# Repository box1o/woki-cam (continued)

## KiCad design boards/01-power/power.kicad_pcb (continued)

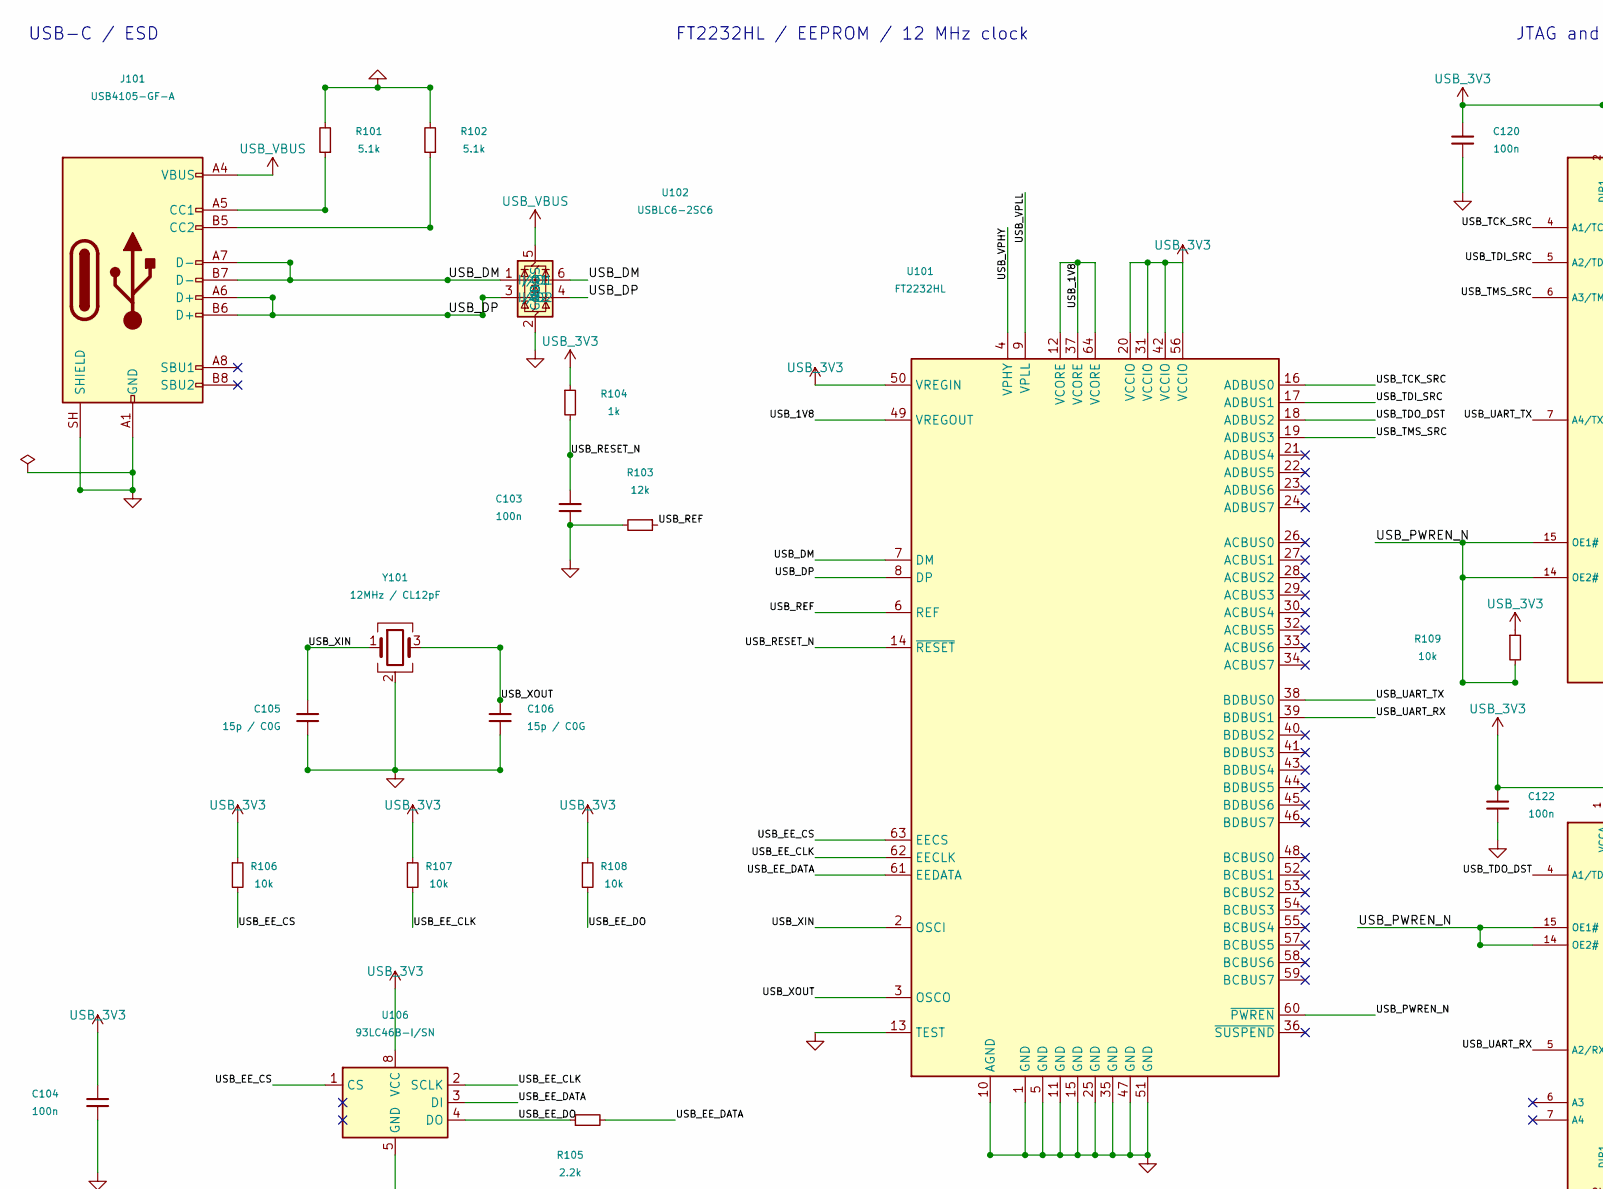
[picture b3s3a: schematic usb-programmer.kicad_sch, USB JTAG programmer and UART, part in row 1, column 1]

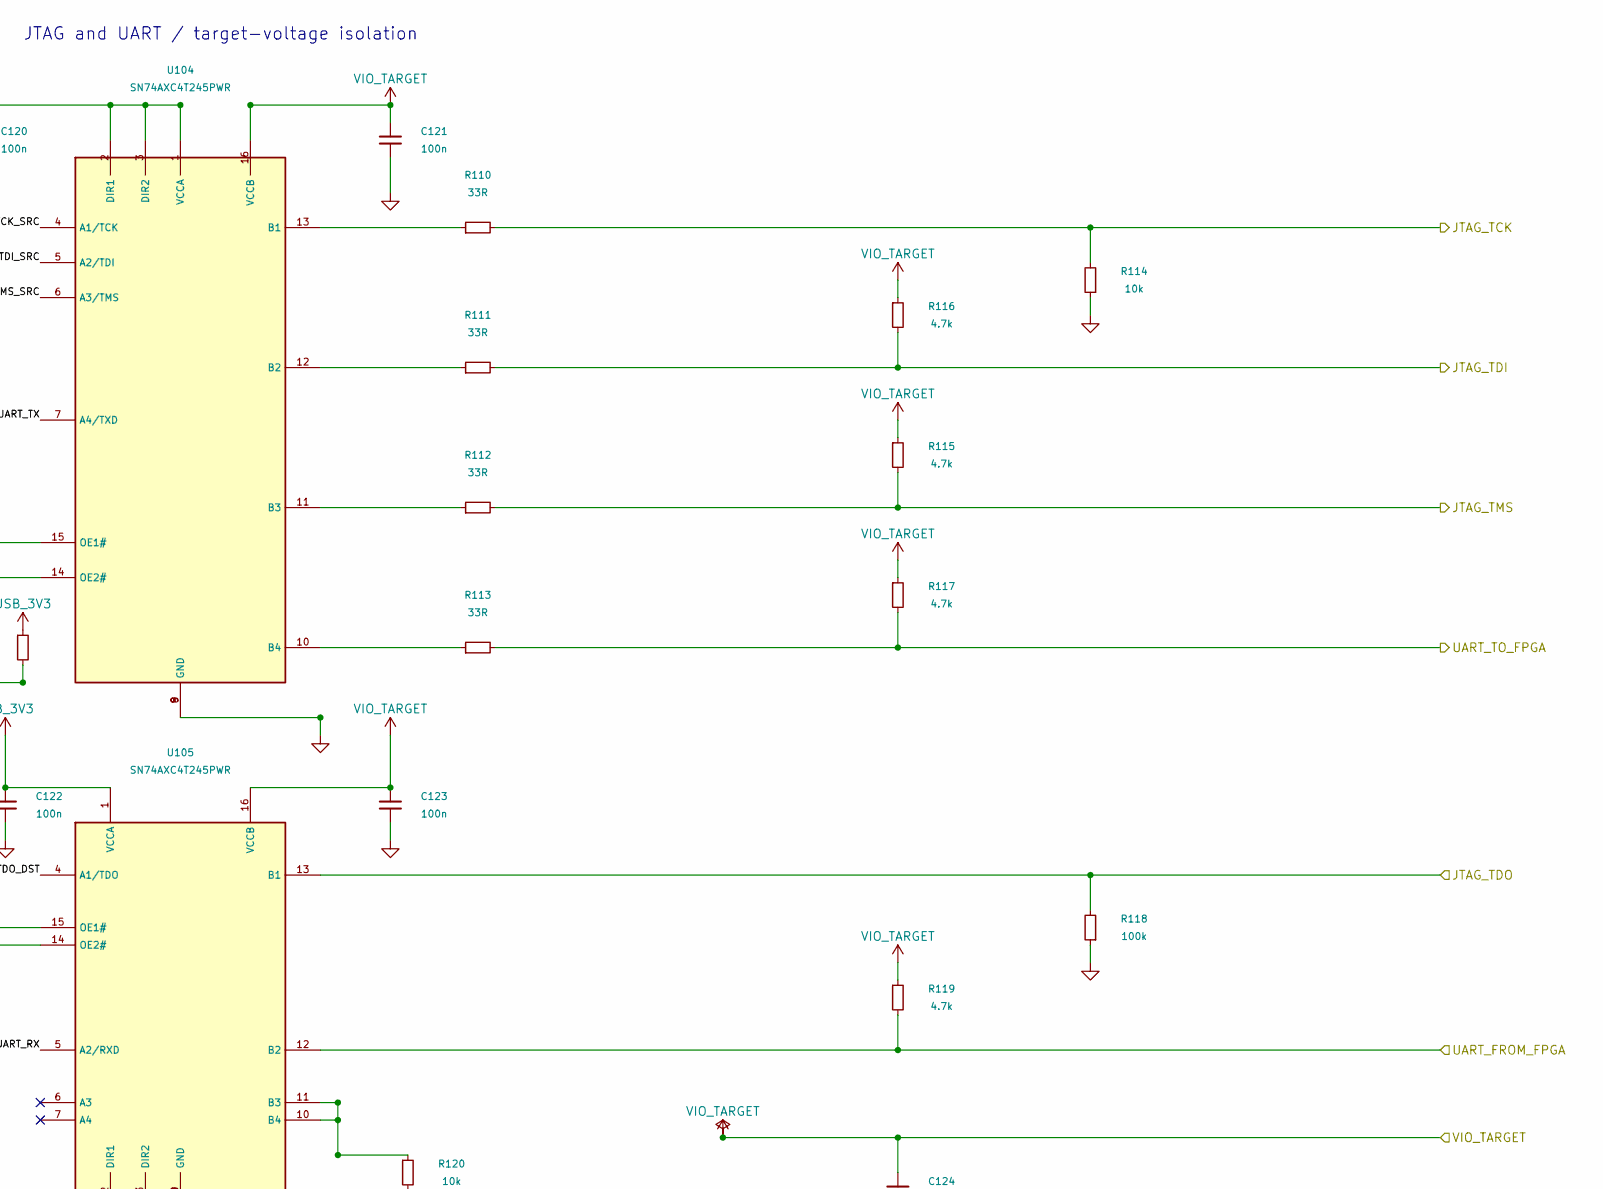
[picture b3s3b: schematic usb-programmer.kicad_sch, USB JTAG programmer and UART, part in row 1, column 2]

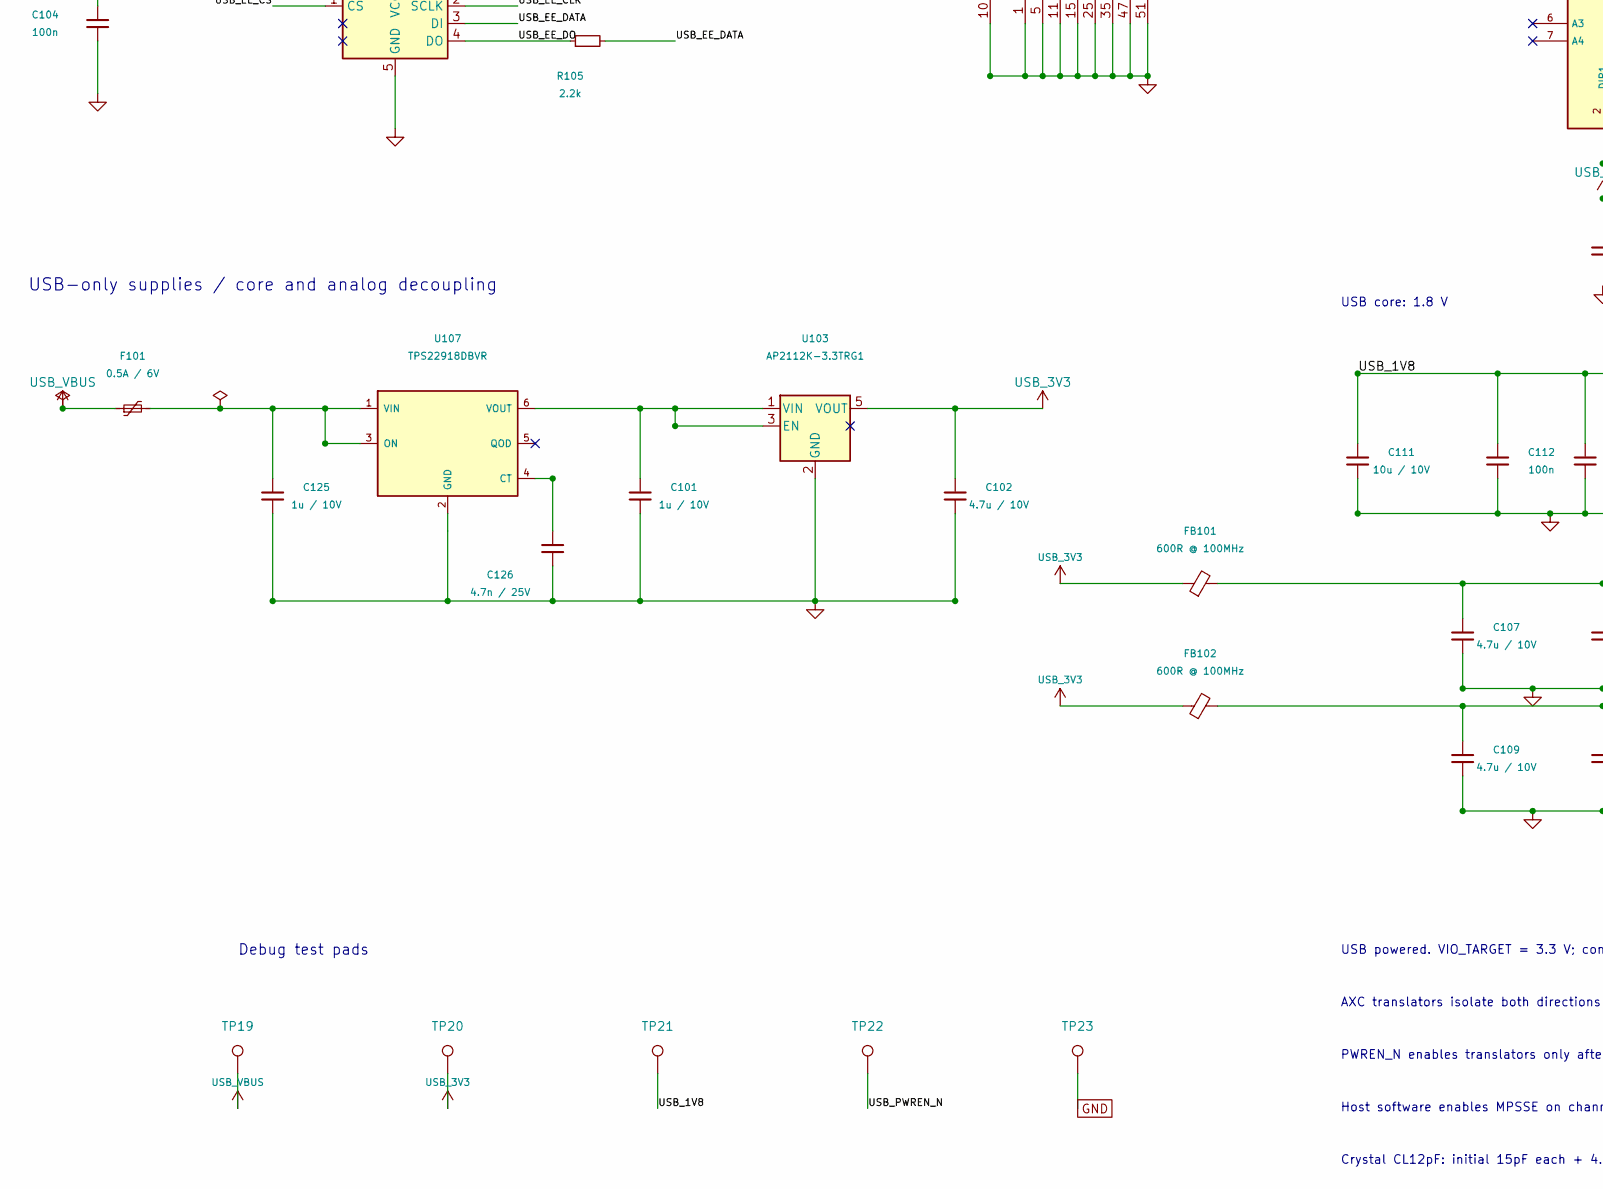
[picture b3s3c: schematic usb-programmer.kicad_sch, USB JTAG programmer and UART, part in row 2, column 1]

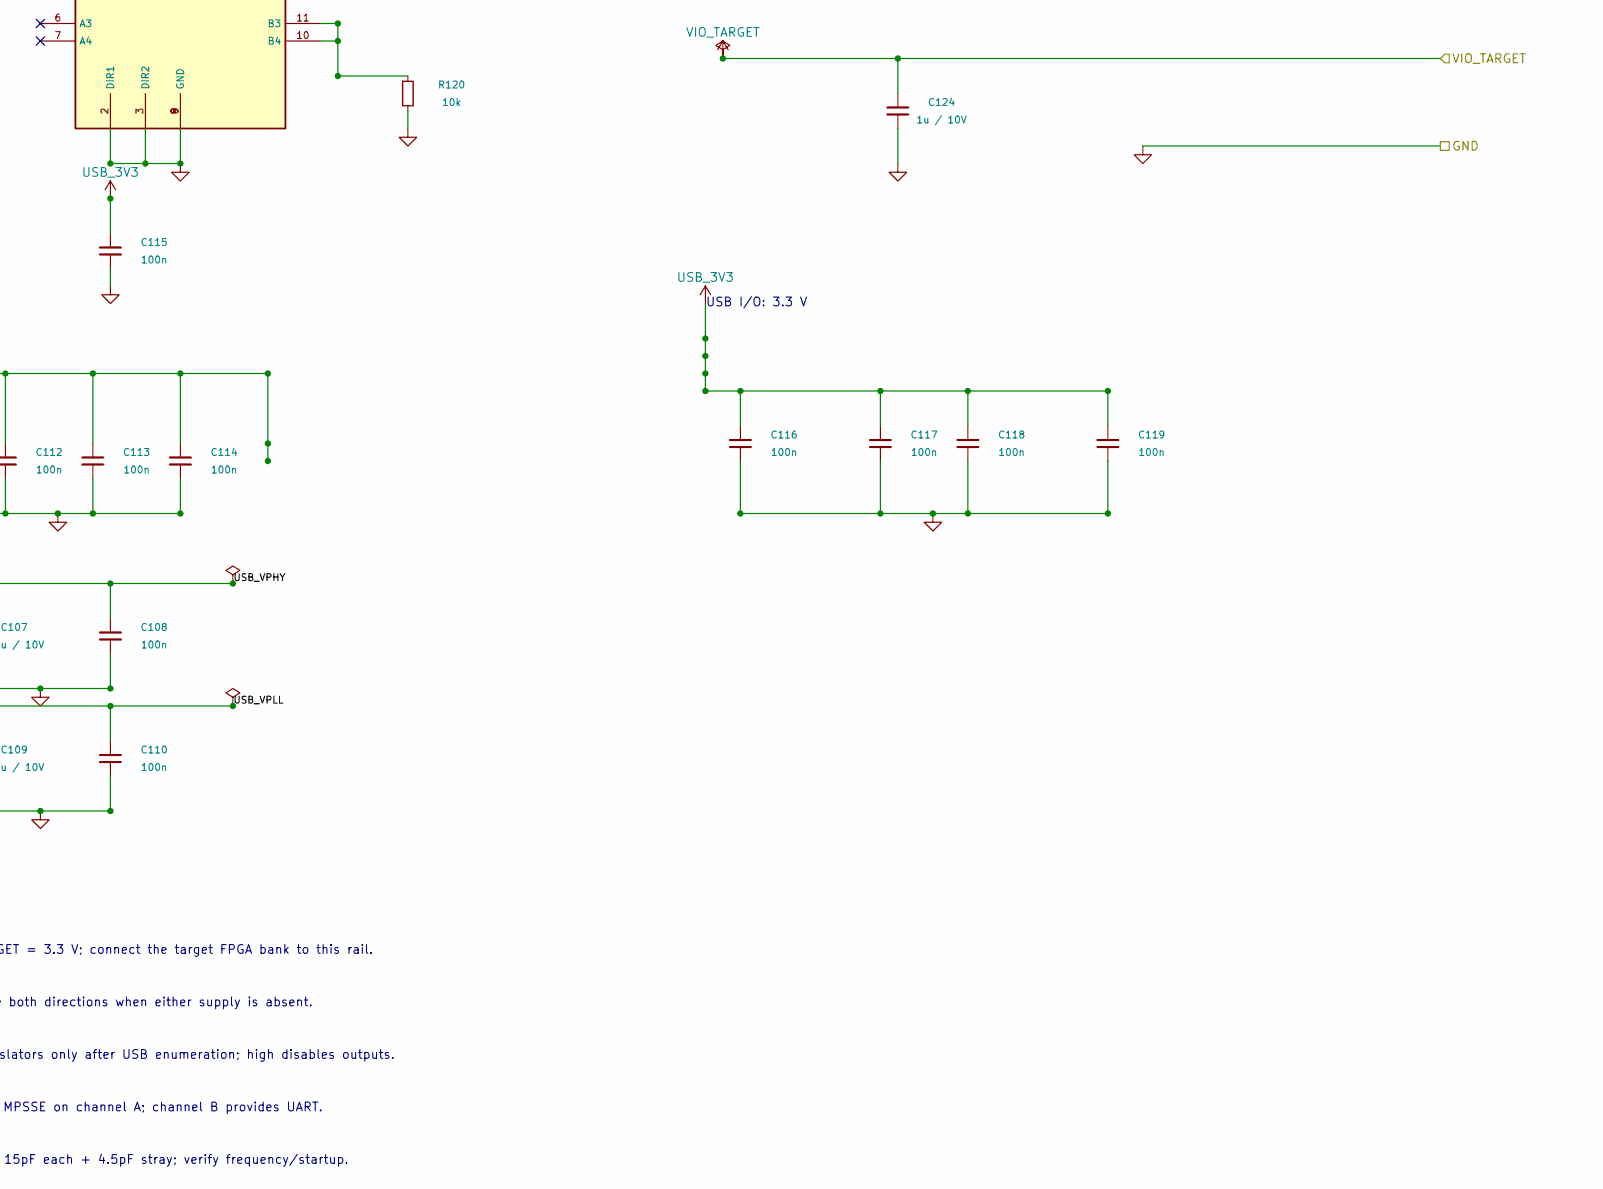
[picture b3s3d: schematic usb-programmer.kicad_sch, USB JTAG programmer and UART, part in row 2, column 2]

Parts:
C101, C124, C125: 1u / 10V; C_0603_1608Metric
C102, C107, C109: 4.7u / 10V; C_0603_1608Metric
C103, C104, C108, C110, C112, C113, C114, C115, C116, C117, C118, C119, C120, C121, C122, C123: 100n; C_0603_1608Metric
C105, C106: 15p / C0G; C_0603_1608Metric
C111: 10u / 10V; C_0805_2012Metric
C126: 4.7n / 25V; C_0603_1608Metric
F101: 0.5A / 6V; Fuse_1206_3216Metric
FB101, FB102: 600R @ 100MHz; L_0603_1608Metric
J101: USB4105-GF-A; USB_C_Receptacle_GCT_USB4105-xx-A_16P_TopMnt_Horizontal
R101, R102: 5.1k; R_0603_1608Metric
R103: 12k; R_0603_1608Metric
R104: 1k; R_0603_1608Metric
R105: 2.2k; R_0603_1608Metric
R106, R107, R108, R109, R114, R120: 10k; R_0603_1608Metric
R110, R111, R112, R113: 33R; R_0603_1608Metric
R115, R116, R117, R119: 4.7k; R_0603_1608Metric
R118: 100k; R_0603_1608Metric
TP19: USB_VBUS; testpoint-pad-1.5mm
TP20: USB_3V3; testpoint-pad-1.5mm
TP21: USB_1V8; testpoint-pad-1.5mm
TP22: USB_PWREN_N; testpoint-pad-1.5mm
TP23: GND; testpoint-pad-1.5mm
U101: FT2232HL; LQFP-64_10x10mm_P0.5mm
U102: USBLC6-2SC6; SOT-23-6
U103: AP2112K-3.3TRG1; SOT-23-5
U104, U105: SN74AXC4T245PWR; TSSOP-16_4.4x5mm_P0.65mm
U106: 93LC46B-I/SN; SOIC-8_3.9x4.9mm_P1.27mm
U107: TPS22918DBVR; SOT-23-6
Y101: 12MHz / CL12pF; Crystal_SMD_3225-4Pin_3.2x2.5mm; MPN ABM8-12.000MHZ-12-B1U-T

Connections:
/JTAG_TCK: R110.2, R114.2; also elsewhere on the board
/JTAG_TDI: R111.2, R116.2; also elsewhere on the board
/JTAG_TDO: R118.2, U105.13 (B1); also elsewhere on the board
/JTAG_TMS: R112.2, R115.2; also elsewhere on the board
/UART_FROM_FPGA: R119.2, U105.12 (B2); also elsewhere on the board
/UART_TO_FPGA: R113.2, R117.2; also elsewhere on the board
/USB JTAG / UART/USB_1V8: C111.1, C112.1, C113.1, C114.1, TP21.1 (1_1), U101.12 (VCORE), U101.37 (VCORE), U101.49 (VREGOUT), U101.64 (VCORE)
/USB JTAG / UART/USB_DM: J101.A7 (D-), J101.B7 (D-), U101.7 (DM), U102.1 (I/O1), U102.6 (I/O1)
/USB JTAG / UART/USB_DP: J101.A6 (D+), J101.B6 (D+), U101.8 (DP), U102.3 (I/O2), U102.4 (I/O2)
/USB JTAG / UART/USB_EE_CLK: R107.2, U101.62 (EECLK), U106.2 (SCLK)
/USB JTAG / UART/USB_EE_CS: R106.2, U101.63 (EECS), U106.1 (CS)
/USB JTAG / UART/USB_EE_DATA: R105.2, U101.61 (EEDATA), U106.3 (DI)
/USB JTAG / UART/USB_EE_DO: R105.1, R108.2, U106.4 (DO)
/USB JTAG / UART/USB_PWREN_N: R109.2, TP22.1 (1_1), U101.60 (~PWREN), U104.14 (OE2#), U104.15 (OE1#), U105.14 (OE2#), U105.15 (OE1#)
/USB JTAG / UART/USB_REF: R103.1, U101.6 (REF)
/USB JTAG / UART/USB_RESET_N: C103.1, R104.2, U101.14 (~RESET)
/USB JTAG / UART/USB_TCK_SRC: U101.16 (ADBUS0), U104.4 (A1/TCK)
/USB JTAG / UART/USB_TDI_SRC: U101.17 (ADBUS1), U104.5 (A2/TDI)
/USB JTAG / UART/USB_TDO_DST: U101.18 (ADBUS2), U105.4 (A1/TDO)
/USB JTAG / UART/USB_TMS_SRC: U101.19 (ADBUS3), U104.6 (A3/TMS)
/USB JTAG / UART/USB_UART_RX: U101.39 (BDBUS1), U105.5 (A2/RXD)
/USB JTAG / UART/USB_UART_TX: U101.38 (BDBUS0), U104.7 (A4/TXD)
/USB JTAG / UART/USB_VPHY: C107.1, C108.1, FB101.2, U101.4 (VPHY)
/USB JTAG / UART/USB_VPLL: C109.1, C110.1, FB102.2, U101.9 (VPLL)
/USB JTAG / UART/USB_XIN: C105.1, U101.2 (OSCI), Y101.1
/USB JTAG / UART/USB_XOUT: C106.1, U101.3 (OSCO), Y101.3
unnamed: J101.A5 (CC1), R101.1
unnamed: J101.B5 (CC2), R102.1
unnamed: C101.1, U103.1 (VIN), U103.3 (EN), U107.6 (VOUT)
unnamed: R110.1, U104.13 (B1)
unnamed: R111.1, U104.12 (B2)
unnamed: R112.1, U104.11 (B3)
unnamed: R113.1, U104.10 (B4)
unnamed: C126.1, U107.4 (CT)
unnamed: C125.1, F101.2, U107.1 (VIN), U107.3 (ON)
USB_3V3: C102.1, C104.1, C115.1, C116.1, C117.1, C118.1, C119.1, C120.1, C122.1, FB101.1, FB102.1, R104.1, R106.1, R107.1, R108.1, R109.1, TP20.1 (1_1), U101.20 (VCCIO), U101.31 (VCCIO), U101.42 (VCCIO), U101.50 (VREGIN), U101.56 (VCCIO), U103.5 (VOUT), U104.1 (VCCA), U104.2 (DIR1), U104.3 (DIR2), U105.1 (VCCA), U106.8 (VCC)
USB_VBUS: F101.1, J101.A4 (VBUS), J101.A9 (VBUS), J101.B4 (VBUS), J101.B9 (VBUS), TP19.1 (1_1), U102.5 (VBUS)
VIO_TARGET: C121.1, C123.1, C124.1, R115.1, R116.1, R117.1, R119.1, U104.16 (VCCB), U105.16 (VCCB); also elsewhere on the board

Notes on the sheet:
USB powered. VIO_TARGET = 3.3 V; connect the target FPGA bank to this rail.
USB core: 1.8 V
JTAG and UART / target-voltage isolation
USB-only supplies / core and analog decoupling
Debug test pads
Crystal CL12pF: initial 15pF each + 4.5pF stray; verify frequency/startup.
USB-C / ESD
Host software enables MPSSE on channel A; channel B provides UART.
USB I/O: 3.3 V
FT2232HL / EEPROM / 12 MHz clock
AXC translators isolate both directions when either supply is absent.
PWREN_N enables translators only after USB enumeration; high disables outputs.

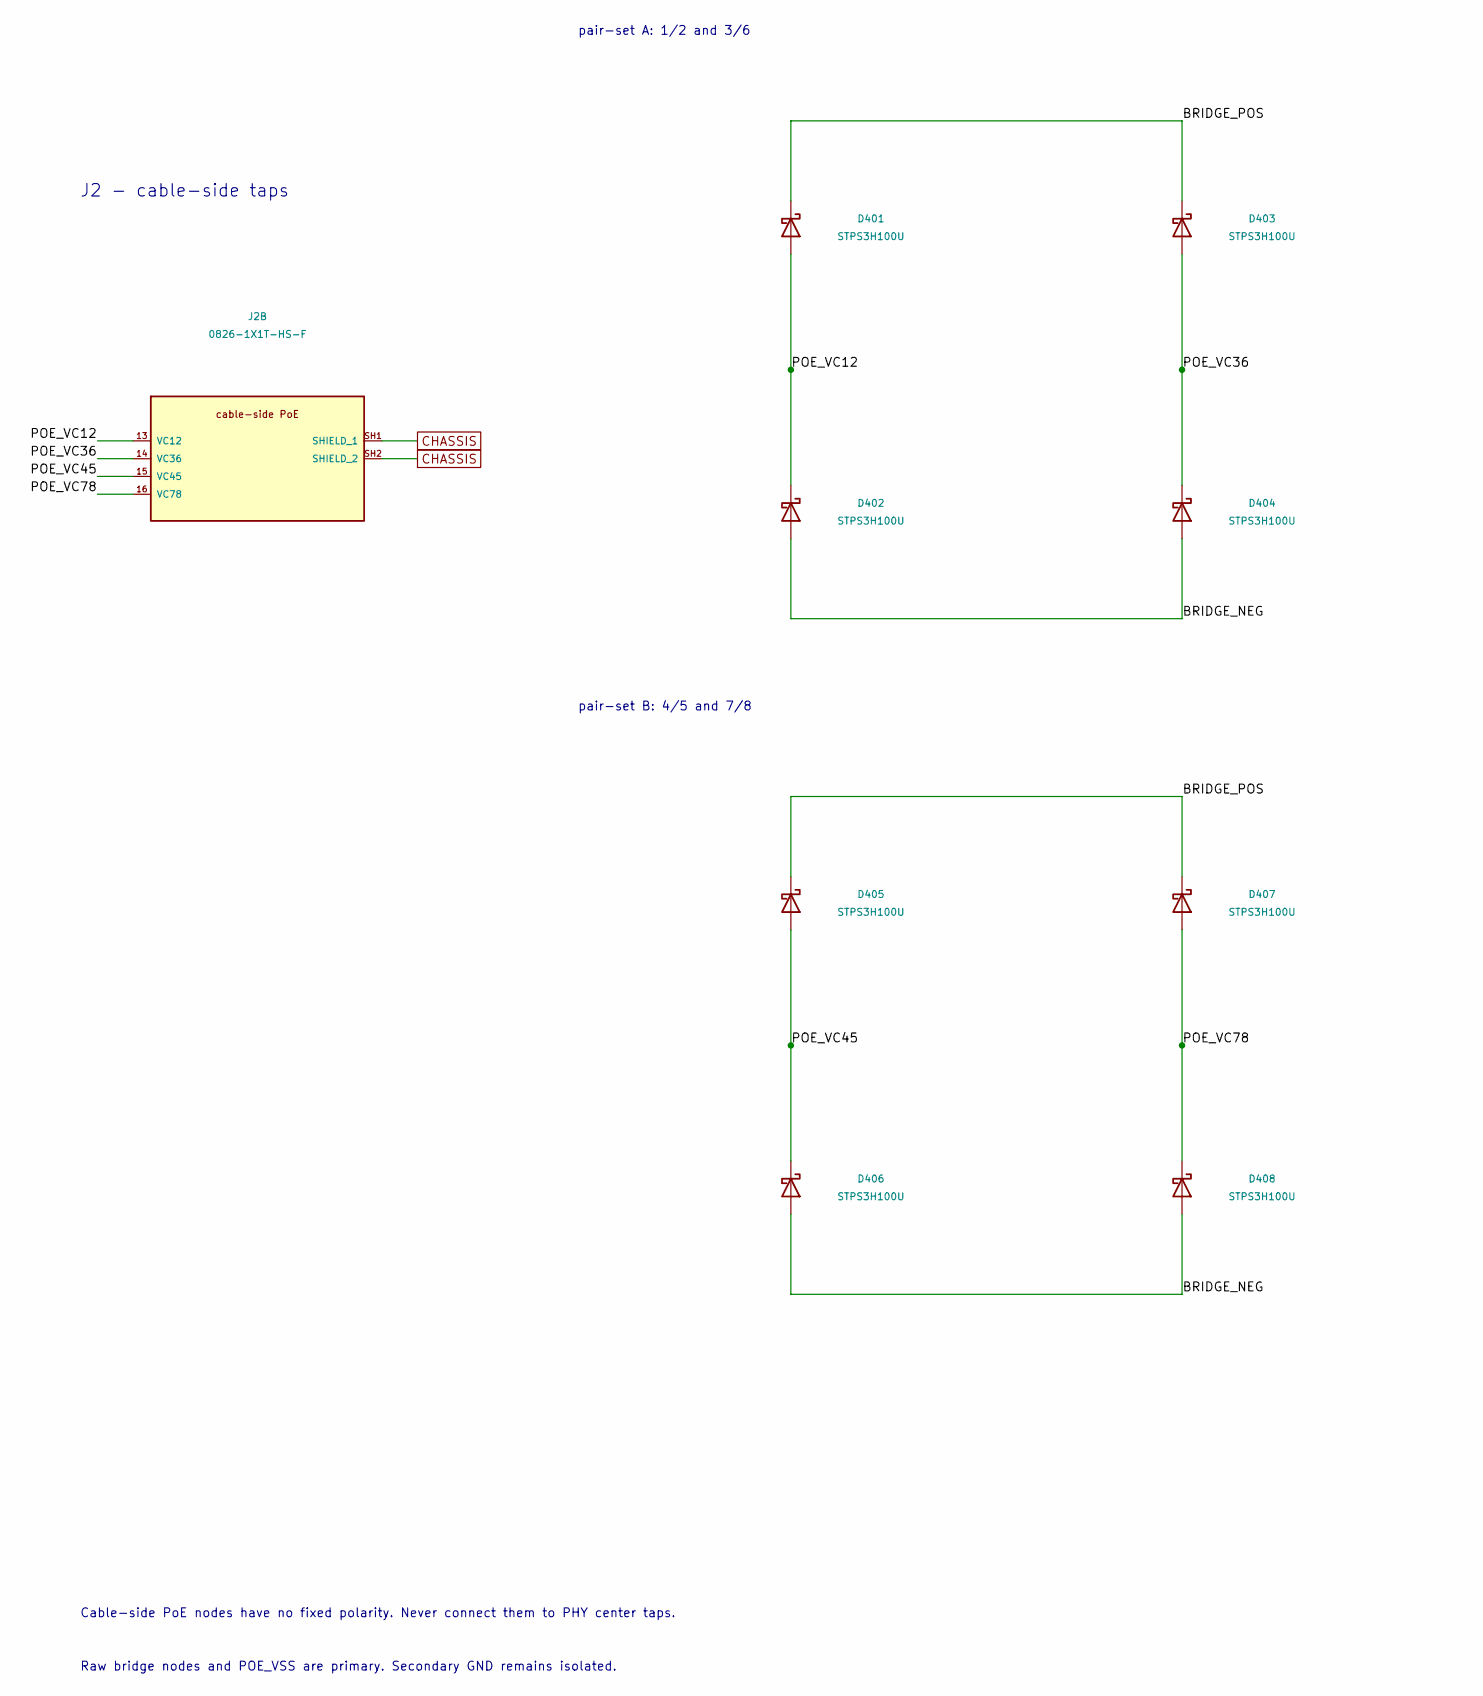
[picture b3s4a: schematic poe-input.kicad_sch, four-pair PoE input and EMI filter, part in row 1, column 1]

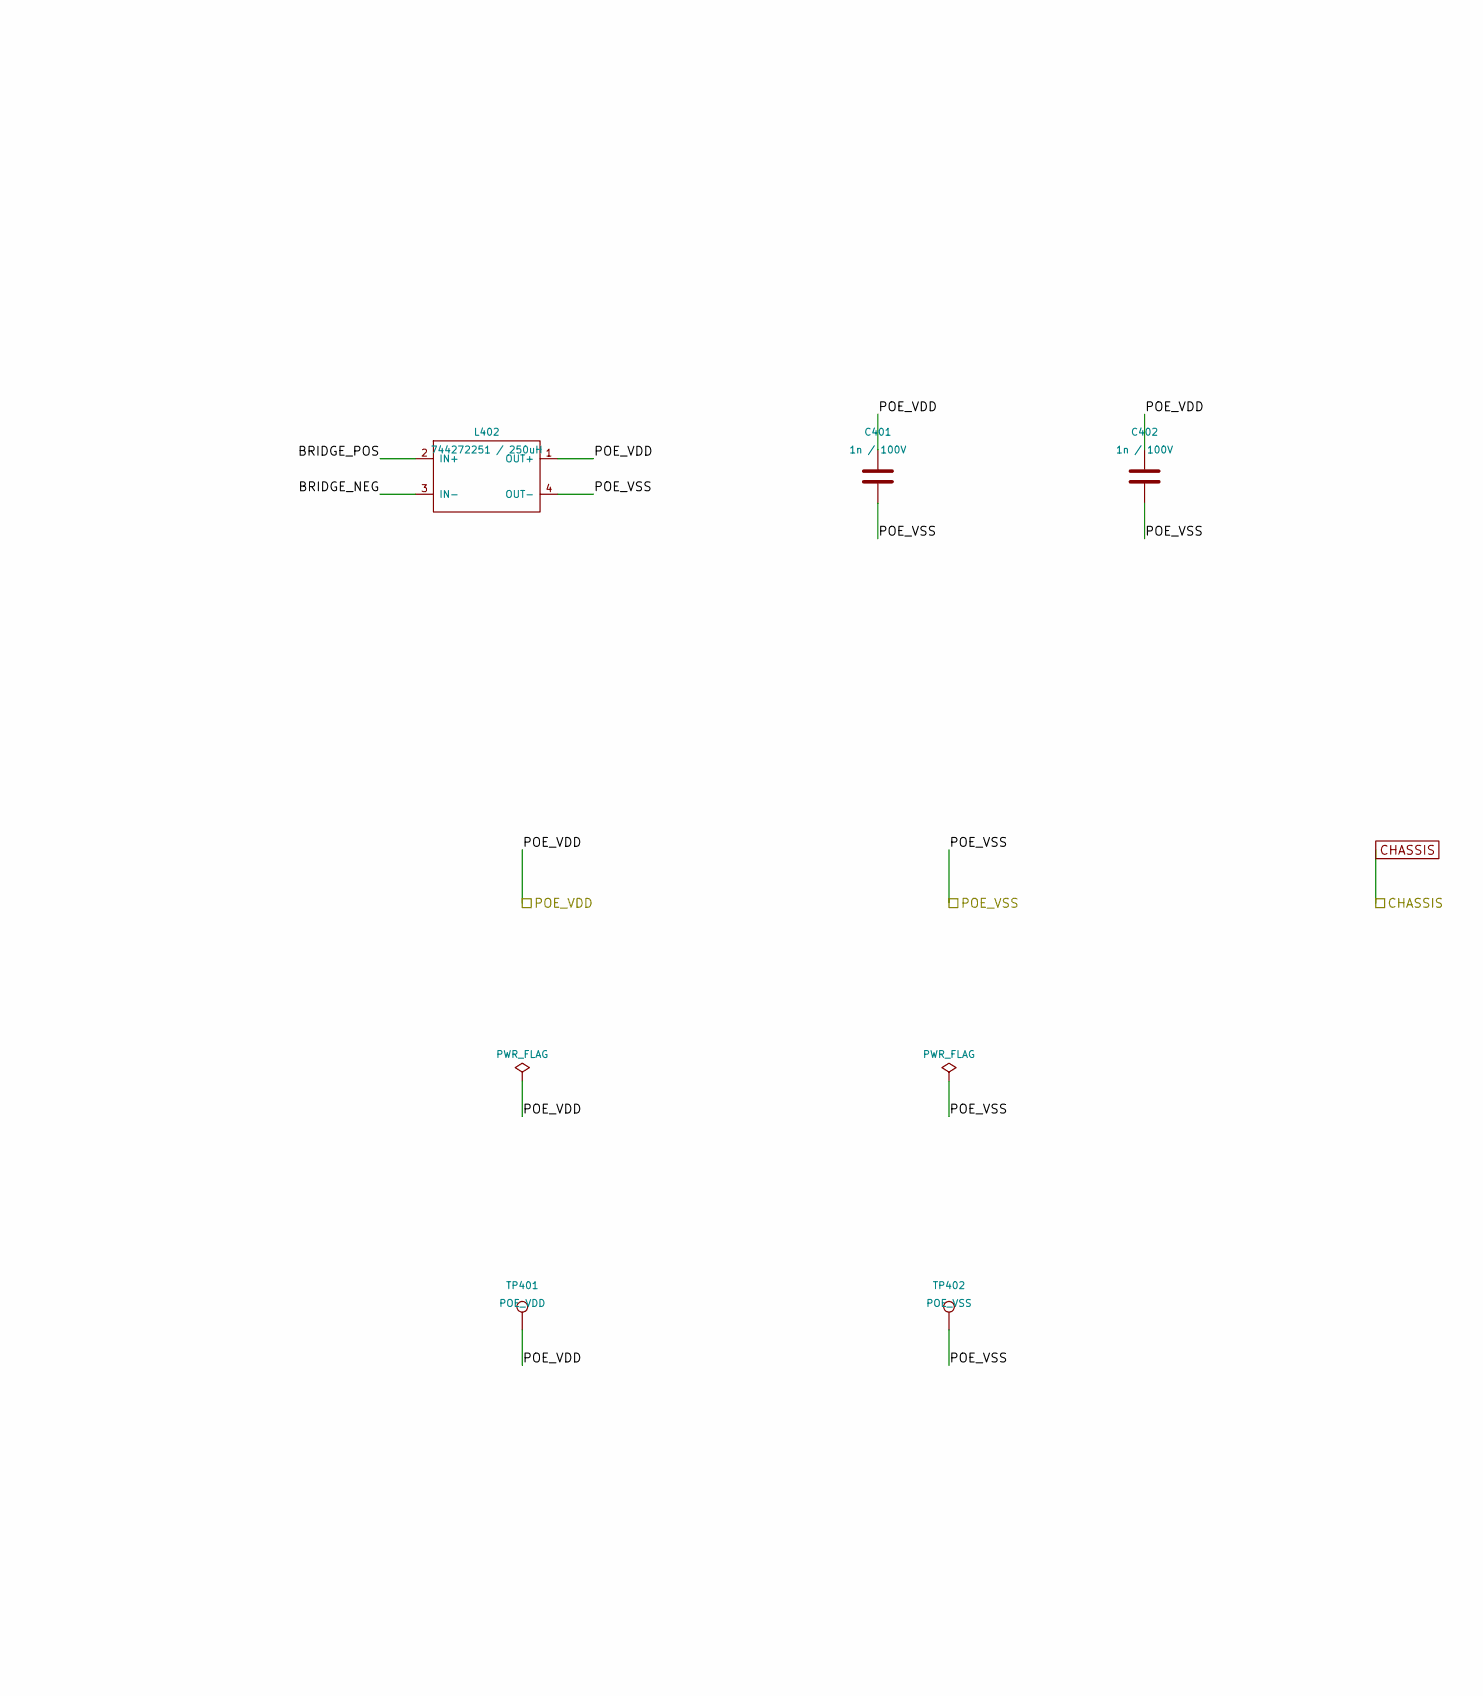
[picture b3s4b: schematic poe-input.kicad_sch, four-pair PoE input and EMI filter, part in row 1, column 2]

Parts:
C401, C402: 1n / 100V; C_0603_1608Metric
D401, D402, D403, D404, D405, D406, D407, D408: STPS3H100U; D_SMB
J2: 0826-1X1T-HS-F; 0826-1x1t-hs-f
L402: 744272251 / 250uH; 744272251
TP401: POE_VDD; TestPoint_Pad_D1.5mm
TP402: POE_VSS; TestPoint_Pad_D1.5mm

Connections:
/MagJack PoE input/BRIDGE_NEG: D402.2 (A), D404.2 (A), D406.2 (A), D408.2 (A), L402.3 (IN-)
/MagJack PoE input/BRIDGE_POS: D401.1 (K), D403.1 (K), D405.1 (K), D407.1 (K), L402.2 (IN+)
/MagJack PoE input/POE_VC12: D401.2 (A), D402.1 (K), J2.13 (VC12)
/MagJack PoE input/POE_VC36: D403.2 (A), D404.1 (K), J2.14 (VC36)
/MagJack PoE input/POE_VC45: D405.2 (A), D406.1 (K), J2.15 (VC45)
/MagJack PoE input/POE_VC78: D407.2 (A), D408.1 (K), J2.16 (VC78)
/POE_VDD: C401.1, C402.1, L402.1 (OUT+), TP401.1 (1_1); also elsewhere on the board
/POE_VSS: C401.2, C402.2, L402.4 (OUT-), TP402.1 (1_1); also elsewhere on the board
CHASSIS: J2.SH1 (SHIELD_1), J2.SH2 (SHIELD_2); also elsewhere on the board

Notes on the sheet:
J2 - cable-side taps
pair-set A: 1/2 and 3/6
Cable-side PoE nodes have no fixed polarity. Never connect them to PHY center taps.
Raw bridge nodes and POE_VSS are primary. Secondary GND remains isolated.
pair-set B: 4/5 and 7/8

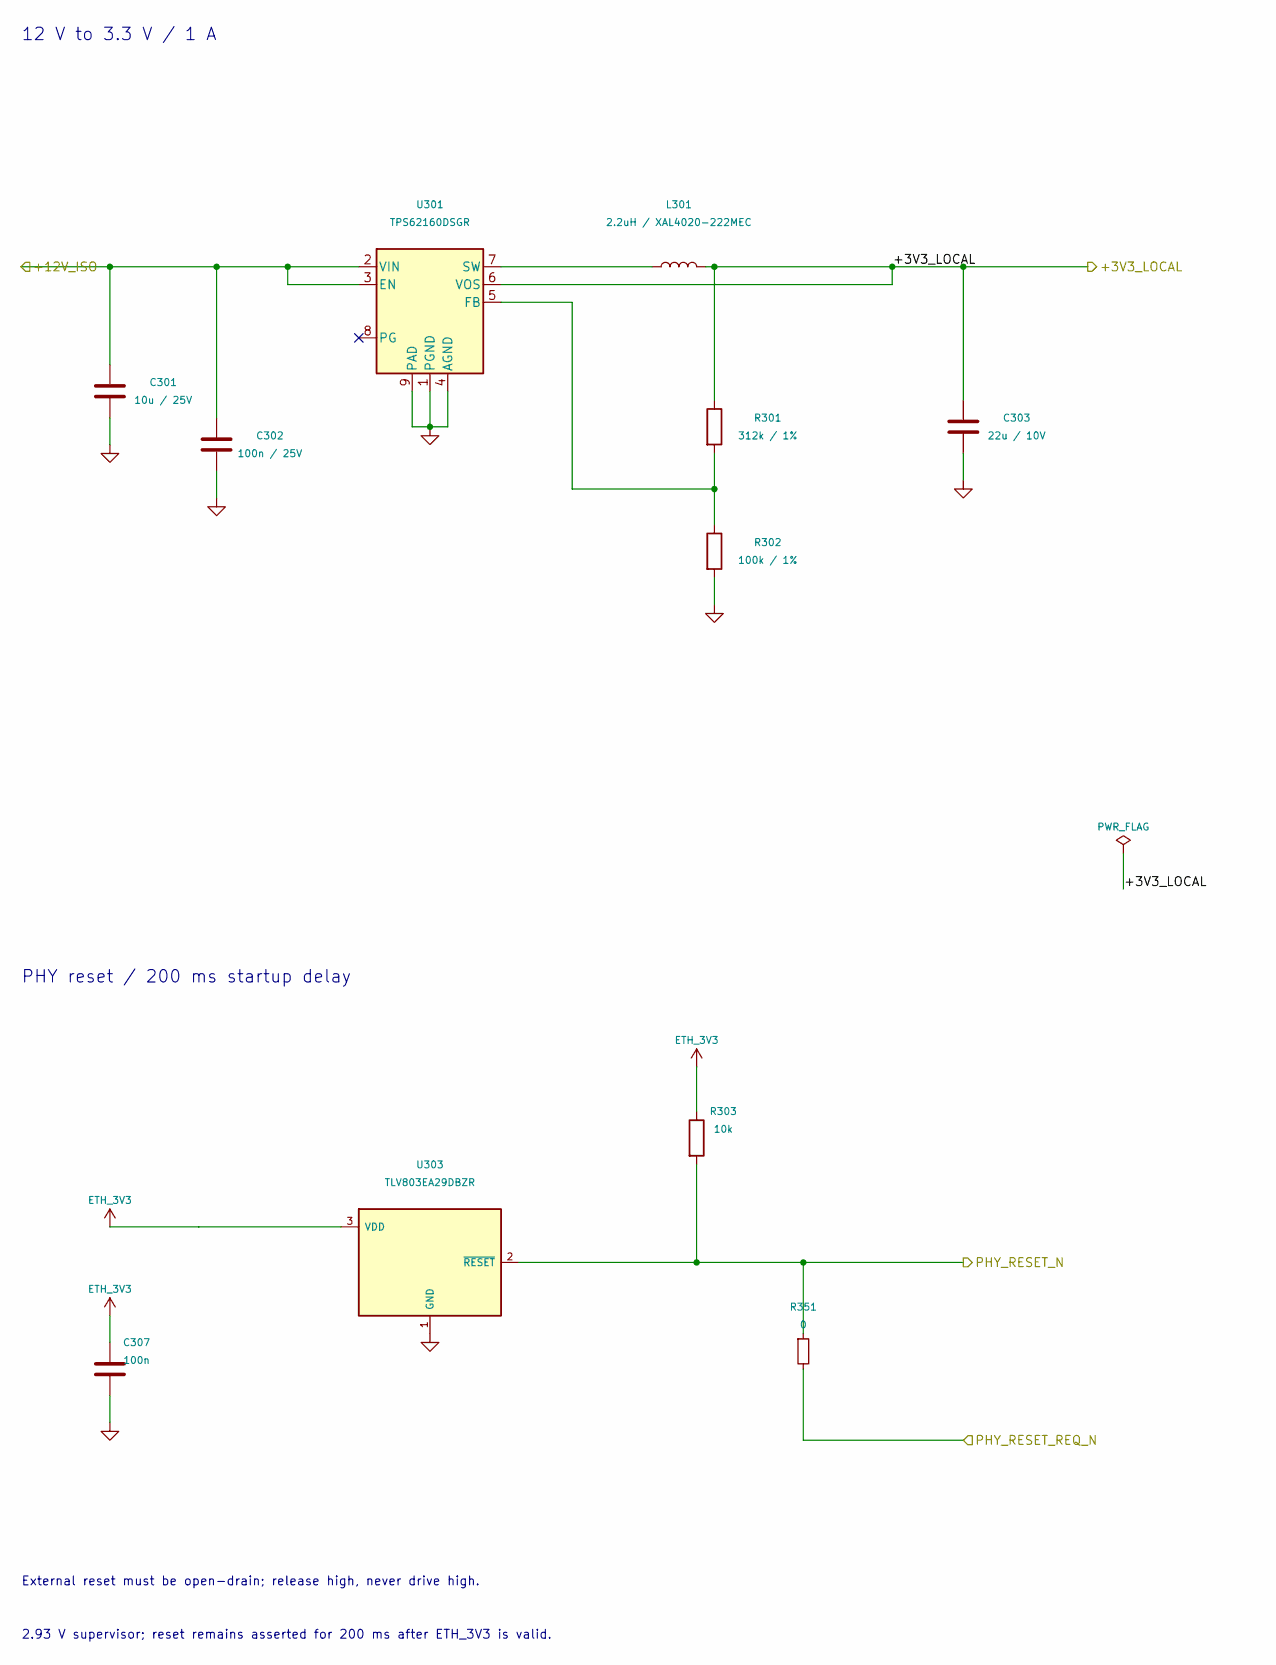
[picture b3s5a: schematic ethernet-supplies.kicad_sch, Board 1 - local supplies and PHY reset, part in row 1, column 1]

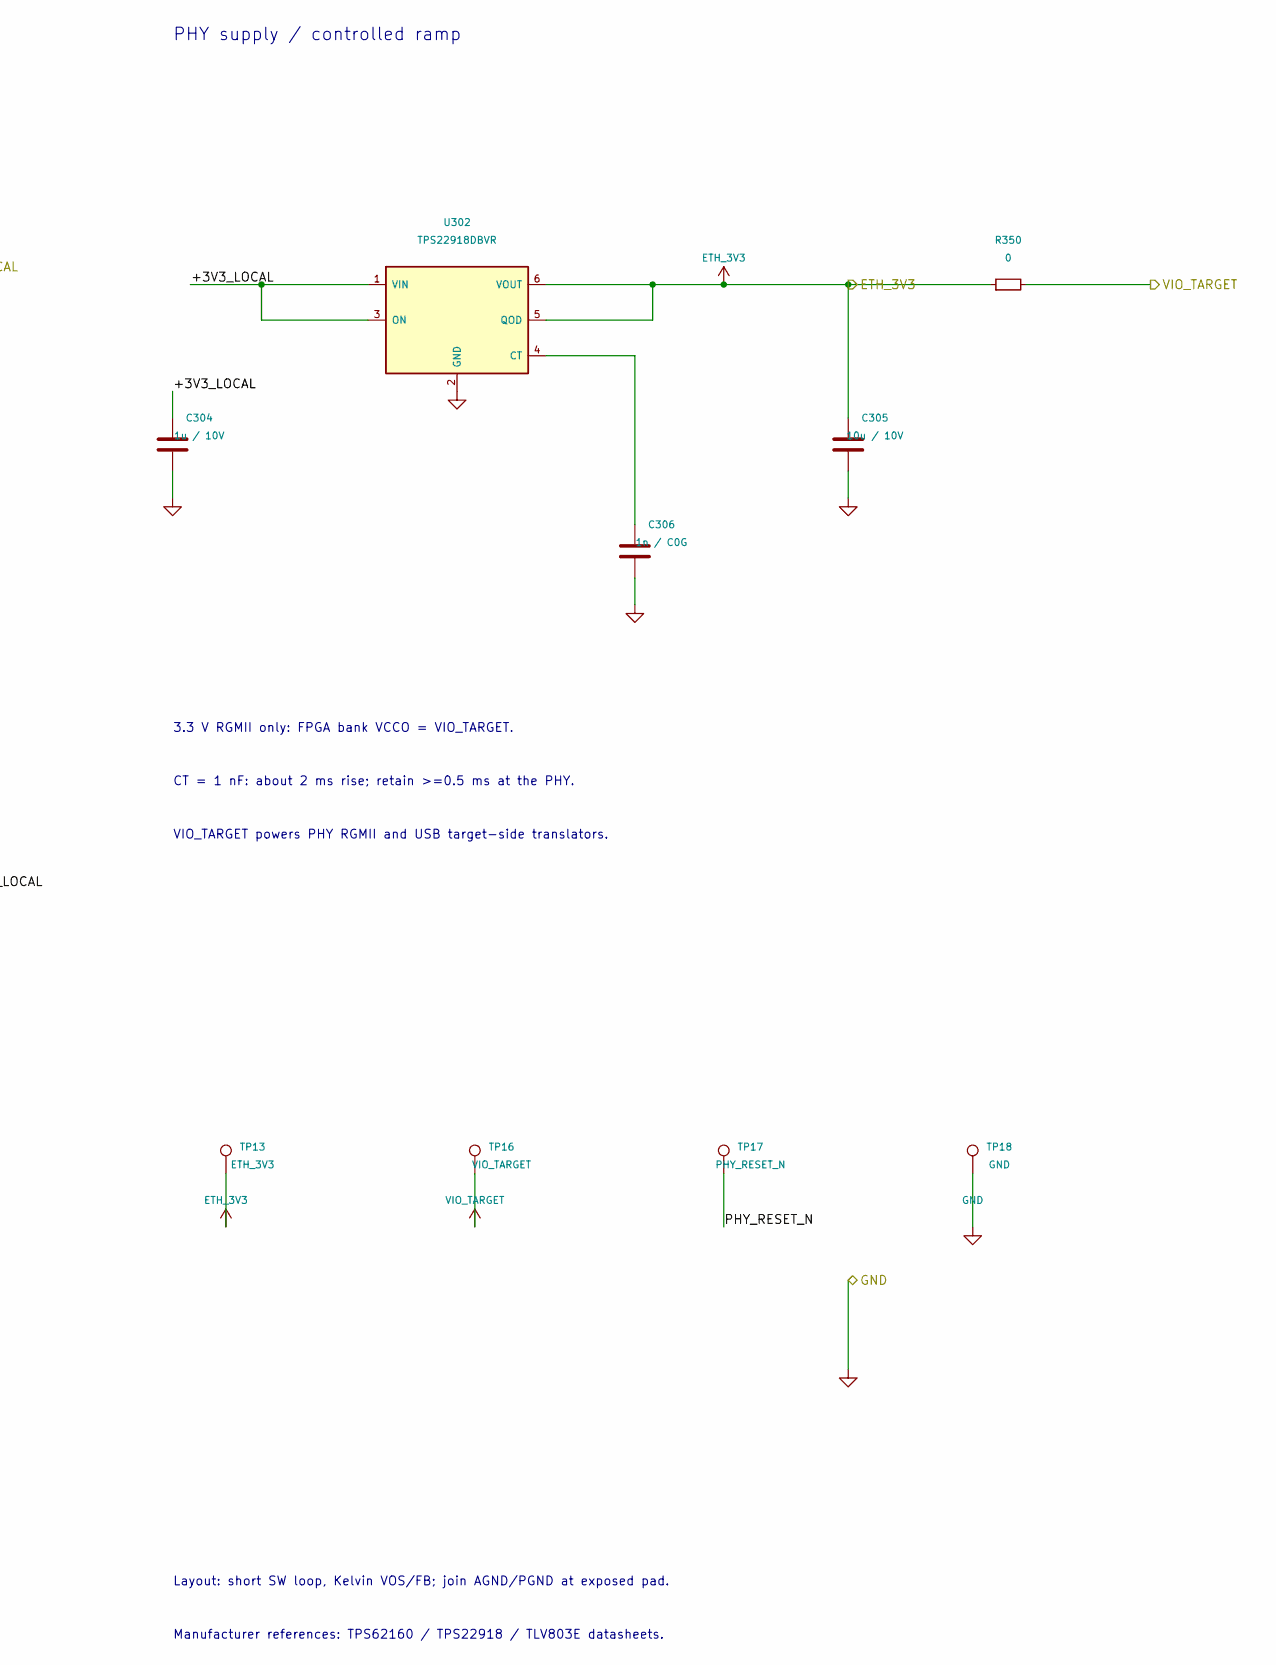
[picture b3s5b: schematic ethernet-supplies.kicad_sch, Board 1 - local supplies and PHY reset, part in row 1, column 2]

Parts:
C301: 10u / 25V; C_0805_2012Metric
C302: 100n / 25V; C_0603_1608Metric
C303: 22u / 10V; C_0805_2012Metric
C304: 1u / 10V; C_0603_1608Metric
C305: 10u / 10V; C_0805_2012Metric
C306: 1n / C0G; C_0603_1608Metric
C307: 100n; C_0603_1608Metric
L301: 2.2uH / XAL4020-222MEC; L_Coilcraft_XAL4020-XXX
R301: 312k / 1%; R_0603_1608Metric
R302: 100k / 1%; R_0603_1608Metric
R303: 10k; R_0603_1608Metric
R350, R351: 0; R_0603_1608Metric
TP13: ETH_3V3; TestPoint_Pad_D1.0mm
TP16: VIO_TARGET; TestPoint_Pad_D1.0mm
TP17: PHY_RESET_N; TestPoint_Pad_D1.0mm
TP18: GND; TestPoint_Pad_D1.0mm
U301: TPS62160DSGR; tps62160dsgr
U302: TPS22918DBVR; SOT-23-6
U303: TLV803EA29DBZR; SOT-23

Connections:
+12V_ISO: C301.1, C302.1, U301.2 (VIN), U301.3 (EN); also elsewhere on the board
/+3V3_LOCAL: C303.1, C304.1, L301.2, R301.1, U301.6 (VOS), U302.1 (VIN), U302.3 (ON); also elsewhere on the board
/PHY_RESET_N: R303.2, R351.1, TP17.1 (1_1), U303.2 (~RESET); also elsewhere on the board
/PHY_RESET_REQ_N: R351.2; also elsewhere on the board
ETH_3V3: C305.1, C307.1, R303.1, R350.1, TP13.1 (1_1), U302.5 (QOD), U302.6 (VOUT), U303.3 (VDD); also elsewhere on the board
unnamed: R301.2, R302.1, U301.5 (FB)
unnamed: L301.1, U301.7 (SW)
unnamed: C306.1, U302.4 (CT)
VIO_TARGET: R350.2, TP16.1 (1_1); also elsewhere on the board

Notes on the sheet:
PHY supply / controlled ramp
12 V to 3.3 V / 1 A
2.93 V supervisor; reset remains asserted for 200 ms after ETH_3V3 is valid.
CT = 1 nF: about 2 ms rise; retain >=0.5 ms at the PHY.
3.3 V RGMII only: FPGA bank VCCO = VIO_TARGET.
VIO_TARGET powers PHY RGMII and USB target-side translators.
External reset must be open-drain; release high, never drive high.
Layout: short SW loop, Kelvin VOS/FB; join AGND/PGND at exposed pad.
Manufacturer references: TPS62160 / TPS22918 / TLV803E datasheets.
PHY reset / 200 ms startup delay
